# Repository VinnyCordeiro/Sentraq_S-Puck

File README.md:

# Sentraq_S-Puck
Let's make an April's Fool prank true!

On April 1st, 2017, our friend Joshua Young from Sentraq announced the creation of the [Sentraq S-Puck keyboard](https://www.reddit.com/r/MechanicalKeyboards/comments/62wufr/teaser_sentraq_spuck/), a 21-switch circular keyboard.

But the joke is too good to let it restricted to an April's Fool prank, so I'm going to make it real!

All files of this repository are released in the public domain, go wild on them!

## Updates:
April 2, 2017: Released CAD files for sandwich-style 140mm diameter circular case (just a little bigger than a regular CD/DVD). Keep in mind that I've made them in about 30 minutes, it's possible there is something wrong with them. I've tested them with the Big Blue Saw online quote tool, though, and they should be fine. I'm designing to use M3 screws, they come with every computer case and are easy to source, you'll probable just need some M3 standoffs (the middle layers were designed with 8mm diameter standoffs in mind, you'll need to edit the files for other diameters). There is also the EAGLE files for a simple PCB; you will need an external controller to use it, like a Teensy 2.0 or an Arduino Micro. A version with embedded microcontroller is planned.

April 8, 2017: PCB with embedded microcontroller added. It can be programmed with both TMK and QMK firmwares. There's a Bill of Materials (BOM) included with Digi-Key codes for the components.

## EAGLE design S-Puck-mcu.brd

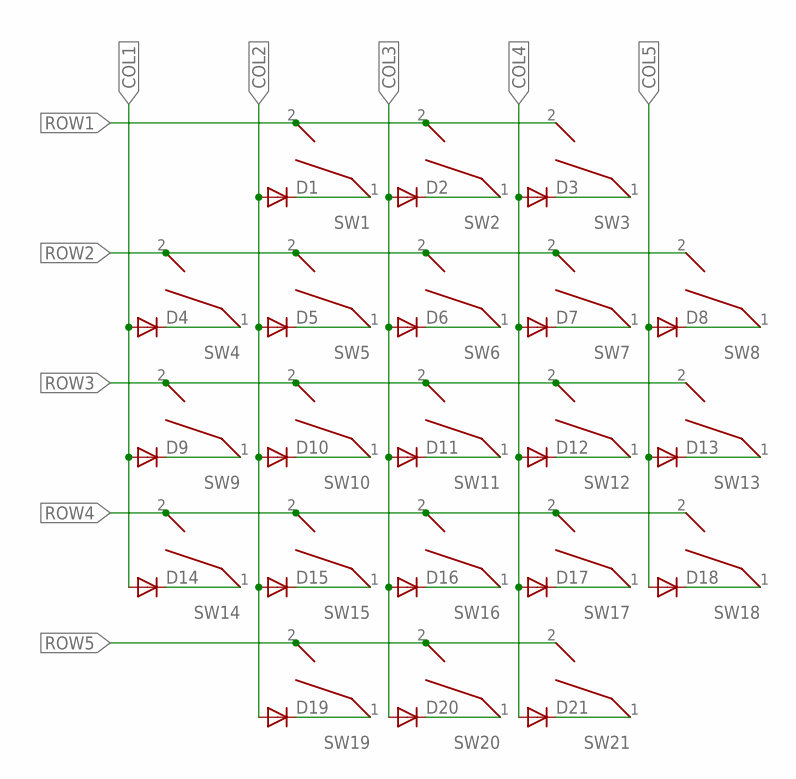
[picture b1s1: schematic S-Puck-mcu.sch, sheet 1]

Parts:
D1, D2, D3, D4, D5, D6, D7, D8, D9, D10, D11, D12, D13, D14, D15, D16, D17, D18, D19, D20, D21: 1N4148DO35-10; DO35-10
SW1, SW2, SW3, SW4, SW5, SW6, SW7, SW8, SW9, SW10, SW11, SW12, SW13, SW14, SW15, SW16, SW17, SW18, SW19, SW20, SW21: CHERRY_MX_WITH_FIXING_PINS; MX1A-XXNW

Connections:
COL1: D4.A, D9.A, D14.A; also elsewhere on the board
COL2: D1.A, D5.A, D10.A, D15.A, D19.A; also elsewhere on the board
COL3: D2.A, D6.A, D11.A, D16.A, D20.A; also elsewhere on the board
COL4: D3.A, D7.A, D12.A, D17.A, D21.A; also elsewhere on the board
COL5: D8.A, D13.A, D18.A; also elsewhere on the board
unnamed: D1.C, SW1.1
unnamed: D2.C, SW2.1
unnamed: D3.C, SW3.1
unnamed: D4.C, SW4.1
unnamed: D5.C, SW5.1
unnamed: D6.C, SW6.1
unnamed: D7.C, SW7.1
unnamed: D8.C, SW8.1
unnamed: D9.C, SW9.1
unnamed: D10.C, SW10.1
unnamed: D11.C, SW11.1
unnamed: D12.C, SW12.1
unnamed: D13.C, SW13.1
unnamed: D14.C, SW14.1
unnamed: D15.C, SW15.1
unnamed: D16.C, SW16.1
unnamed: D17.C, SW17.1
unnamed: D18.C, SW18.1
unnamed: D19.C, SW19.1
unnamed: D20.C, SW20.1
unnamed: D21.C, SW21.1
ROW1: SW1.2, SW2.2, SW3.2; also elsewhere on the board
ROW2: SW4.2, SW5.2, SW6.2, SW7.2, SW8.2; also elsewhere on the board
ROW3: SW9.2, SW10.2, SW11.2, SW12.2, SW13.2; also elsewhere on the board
ROW4: SW14.2, SW15.2, SW16.2, SW17.2, SW18.2; also elsewhere on the board
ROW5: SW19.2, SW20.2, SW21.2; also elsewhere on the board

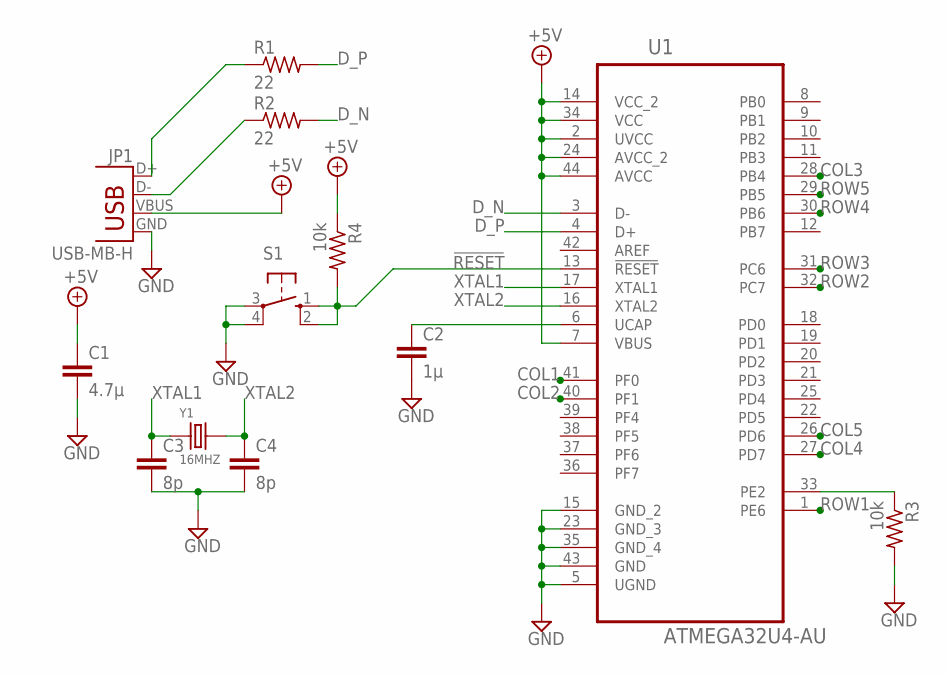
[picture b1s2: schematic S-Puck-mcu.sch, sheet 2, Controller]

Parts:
C1: 4.7µ; C0805K
C2: 1µ; C0805K
C3, C4: 8p; C0805K
JP1: USB-MB-H
R1, R2: 22; R0805W
R3, R4: 10k; R0805W
S1: 10-XX; B3F-10XX
U1: ATMEGA32U4-AU; QFP80P1200X1200X120-44N
Y1: 16MHZ; X2-SMD-5.0X3.2X1.3MM

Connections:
!RESET!: R4.2, S1.1 (S), S1.2 (S1), U1.13 (!RESET!)
+5V: C1.1, JP1.VBUS, R4.1, U1.2 (UVCC), U1.7 (VBUS), U1.14 (VCC_2), U1.24 (AVCC_2), U1.34 (VCC), U1.44 (AVCC)
COL1: U1.41 (PF0); also elsewhere on the board
COL2: U1.40 (PF1); also elsewhere on the board
COL3: U1.28 (PB4); also elsewhere on the board
COL4: U1.27 (PD7); also elsewhere on the board
COL5: U1.26 (PD6); also elsewhere on the board
D_N: R2.2, U1.3 (D-)
D_P: R1.2, U1.4 (D+)
GND: C1.2, C2.2, C3.2, C4.2, JP1.GND, R3.2, S1.3, S1.4 (P1), U1.5 (UGND), U1.15 (GND_2), U1.23 (GND_3), U1.35 (GND_4), U1.43 (GND)
unnamed: JP1.D+, R1.1
unnamed: JP1.D-, R2.1
unnamed: R3.1, U1.33 (PE2)
unnamed: C2.1, U1.6 (UCAP)
ROW1: U1.1 (PE6); also elsewhere on the board
ROW2: U1.32 (PC7); also elsewhere on the board
ROW3: U1.31 (PC6); also elsewhere on the board
ROW4: U1.30 (PB6); also elsewhere on the board
ROW5: U1.29 (PB5); also elsewhere on the board
XTAL1: C3.1, U1.17 (XTAL1), Y1.1
XTAL2: C4.1, U1.16 (XTAL2), Y1.2

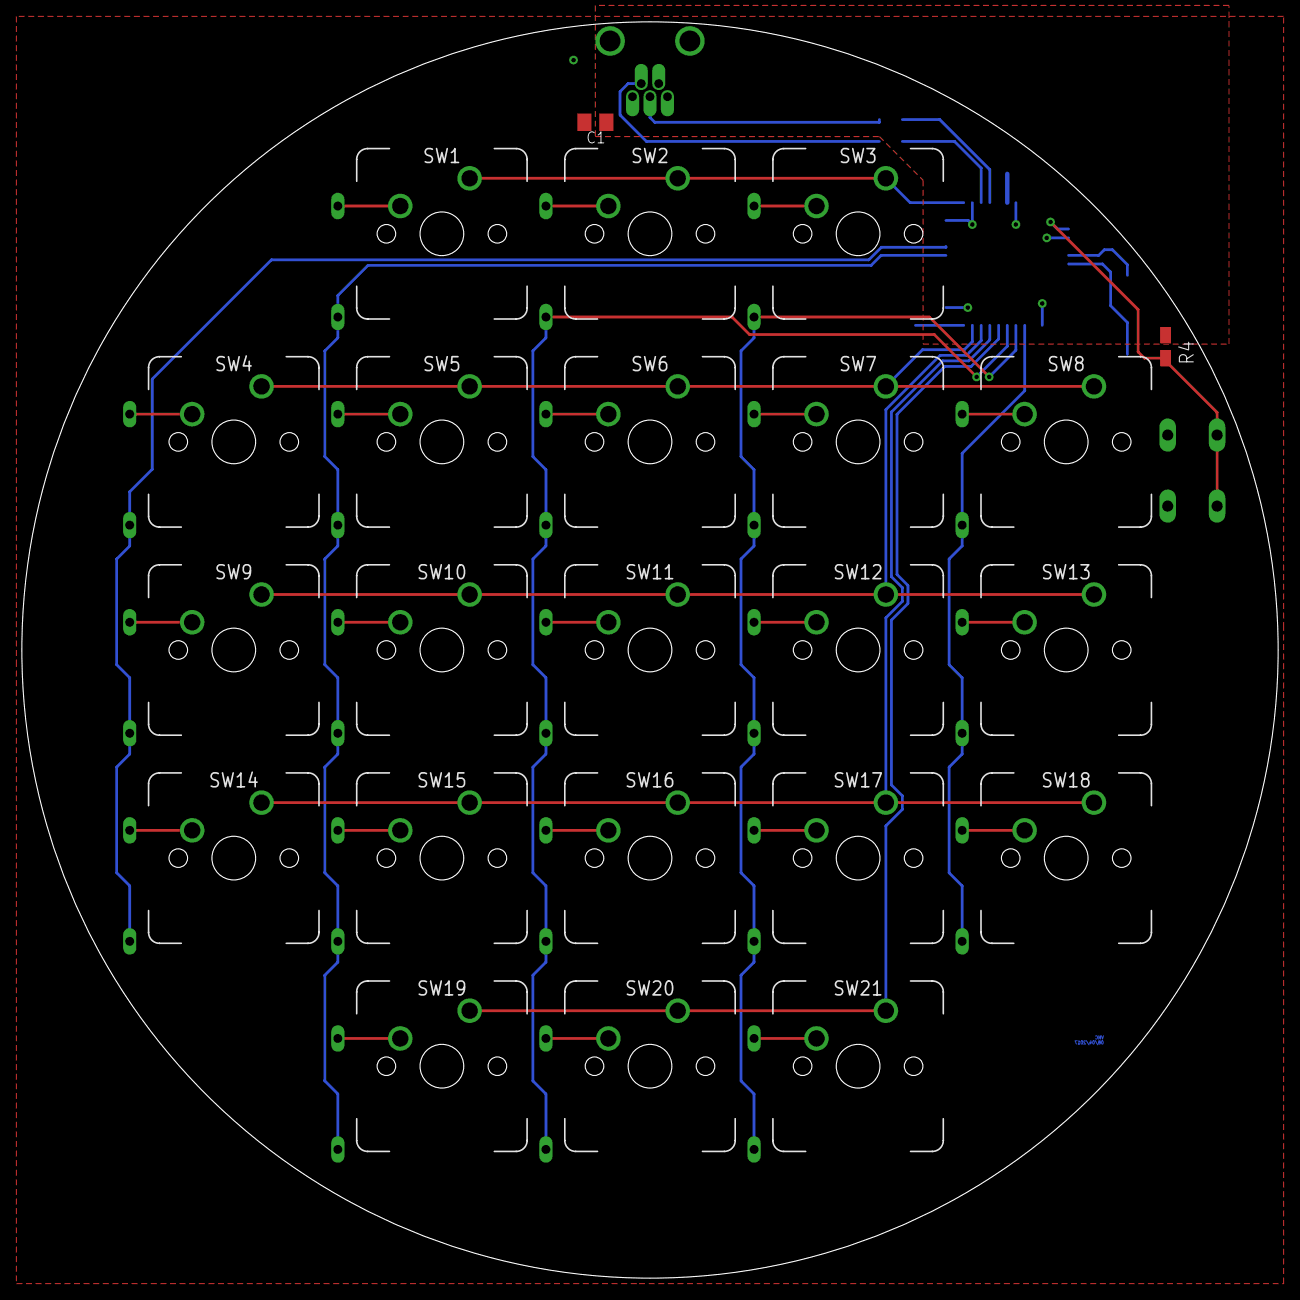
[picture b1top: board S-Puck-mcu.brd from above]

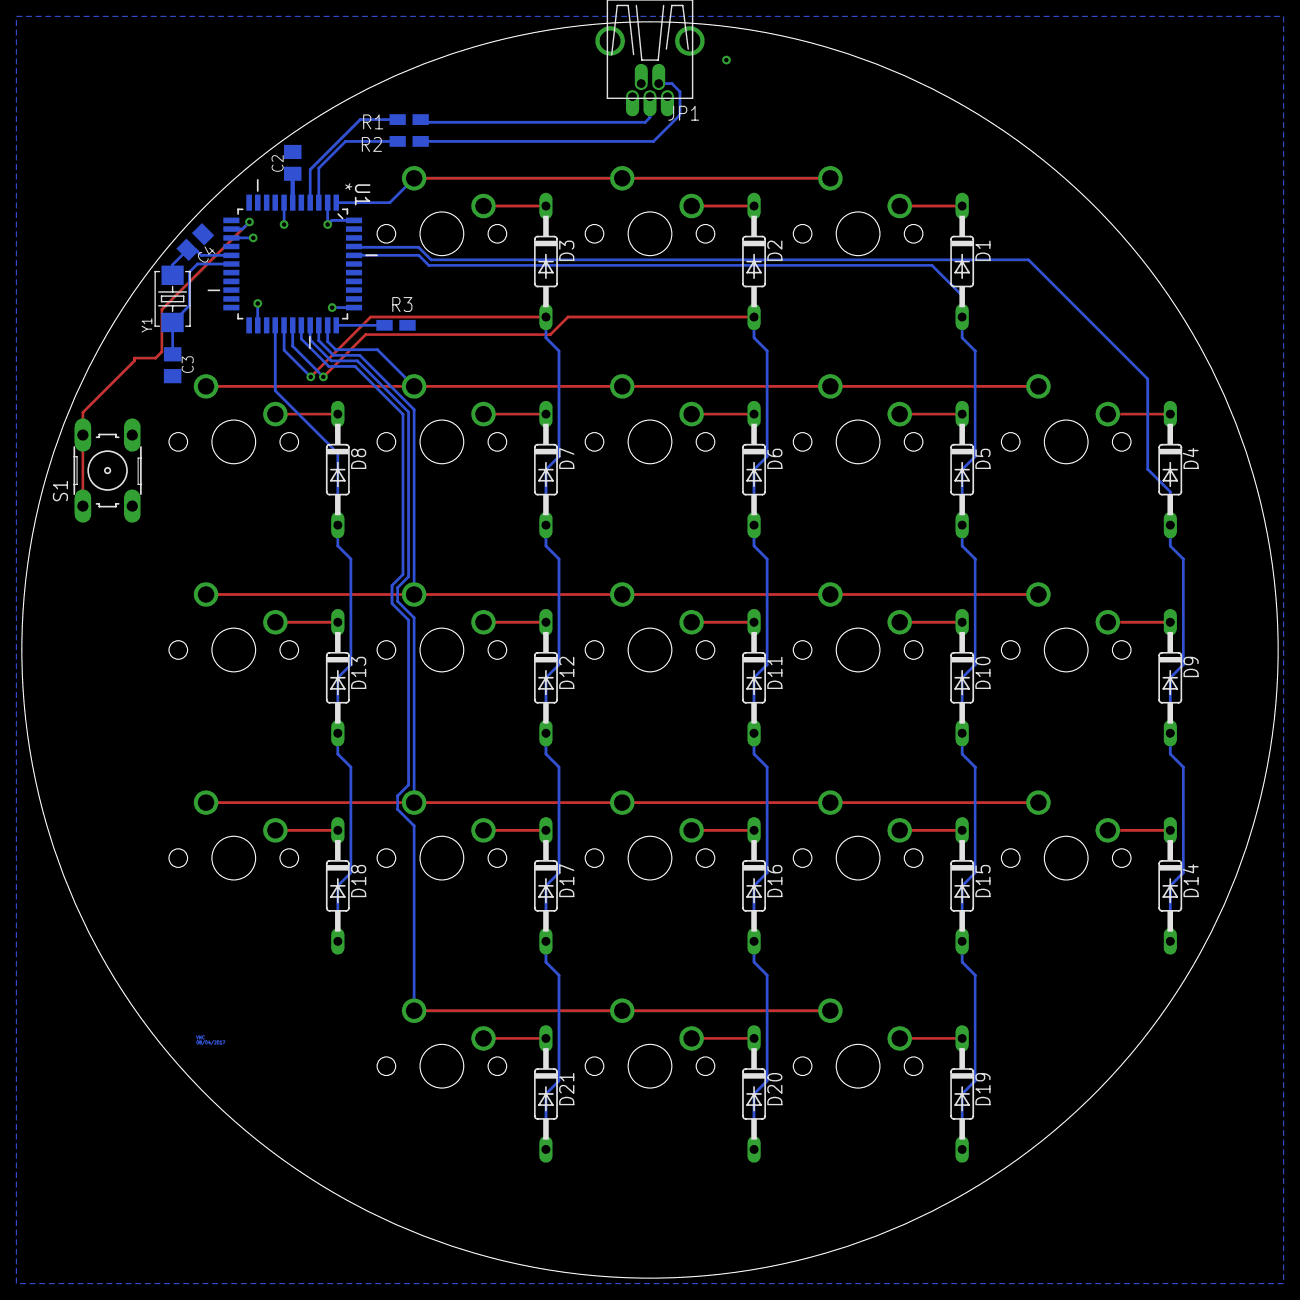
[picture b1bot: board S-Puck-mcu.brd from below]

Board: 2 copper layers, 115.0 x 115.0 mm, 54 parts (31 on the bottom side), 42 nets.

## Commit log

2017-04-02 Initial README update
2017-04-02 Initial commit
    Switch and bottom plates for a sandwich-style case. Designed to use M3 screws.
2017-04-02 Updated CAD files
    Increased size of the case to 140mm diameter, due to fitting problems with the upcoming PCB. Also added middle layers, with and without cutout for USB connector.
2017-04-02 Update README.md
    Changed the size of the case, from 120mm to 140mm in diameter.
2017-04-02 No microcontroler PCB
    First version of a PCB for the S-Puck. This PCB requires an external board, like a Teensy 2.0.
2017-04-02 Update README.md
    Added information about the PCB.
2017-04-02 Rename S-Puck-no_ncu.sch to S-Puck-no_mcu.sch
    Correcting a typo.
2017-04-02 Update README.md
    Added link for the Sentraq S-Puck.
2017-04-09 PCB with embedded microcontroller
    This PCB uses an ATmega32U4 microcontroller that can be programmed with TMK or QMK firmwares.
2017-04-09 Added Bill of Materials (BOM)
2018-07-16 Update LICENSE
    Changed the license to the CERN Open Hardware Licence v1.2

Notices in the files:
parts and their libraries:
SparkFun-Connectors: Licensing: Creative Commons ShareAlike 4.0 International - https://creativecommons.org/licenses/by-sa/4.0
